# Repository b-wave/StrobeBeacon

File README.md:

# LED Strobe / Beacon
Strobe and beacon lights for models using PIC12F1822

This project describes a _realistic-looking_ set of lights for model aircraft. The strobe is typically a white light located at the aft end of the aircraft.  The strobe consists of several quick flashes, repeating after a dark pause. The beacon is a light that flashes once, typically as a red beacon at the top of the airplane's rudder, with a longer on-time duration You can also set up two alternating strobes, such a police or emergency vehicle, where the lights alternate between red and white or red and blue.

## Firmware
The firmware is included in the folder. It is a C source file that was compiled with the  _MPLAB IDE_ V6.00. The .HEX file can be directly programmed, either on the chip itself or using the provided in-circuit programming pins (ICP) on the. If you do not want to compile, you can directly use the provided .HEX file. We used a _TL866 II Plus_ for both. You can use the uploaded StrobeBeacon.X.production.HEX file.

## Hardware

The hardware was developed using KiCAD version 8.0.  

This is a simple circuit board. All the Gerber files are included, but you can order directly from this project file on OSH Park.com: 

https://oshpark.com/shared_projects/jd6ww6b6

## Enhancements
Several features can be added to this.  I will either expand here or make a new repo. 

First to make it useful in an R/C model, the ability to read an R/C receiver's PWM channel can be used switch the strobes on or off. Adding a standard 3-pin 0.1 inch connector allows for direct to an R/C receiver's channel connector. For an Arduino, it is relatively simple to use the pulseIn() from the standard libraries.
```C
byte GetPWM(byte pin)
{
  unsigned long highTime = pulseIn(pin, HIGH, 50000UL);  // 50 millisecond timeout
  unsigned long lowTime = pulseIn(pin, LOW, 50000UL);  // 50 millisecond timeout

  // pulseIn() returns zero on timeout
  if (highTime == 0 || lowTime == 0)
    return digitalRead(pin) ? 100 : 0;  // HIGH == 100%,  LOW = 0%

  return (100 * highTime) / (highTime + lowTime);  // highTime as percentage of total cycle time
}
```

But for a PIC microcontroller it is a little more involved.  We have to use timers and interrrupts.  The CCP1 interrupt can be used to detect the edge. Then the width is timed. 

*Copilot PROMPT: Give an example of pic12f1822 to measure a PWM input*

To measure a PWM input using the PIC12F1822 microcontroller, you can use the Capture/Compare/PWM (CCP) module. Here's a basic example of how you can set it up:

1. Configure the CCP module: Set the CCP module to capture mode to measure the PWM input signal.
2. Configure the Timer: Use Timer1 to capture the PWM signal's period and duty cycle.
3. Capture the PWM signal: Use the CCP module to capture the rising and falling edges of the PWM signal.

Here's a simple code example using MPLAB X IDE and XC8 compiler:
```C
#include <xc.h>

// Configuration bits
#pragma config FOSC = INTOSC    // Oscillator Selection
#pragma config WDTE = OFF       // Watchdog Timer Enable
#pragma config PWRTE = OFF      // Power-up Timer Enable
#pragma config MCLRE = ON       // MCLR Pin Function Select
#pragma config CP = OFF         // Flash Program Memory Code Protection
#pragma config BOREN = ON       // Brown-out Reset Enable
#pragma config CLKOUTEN = OFF   // Clock Out Enable
#pragma config IESO = ON        // Internal/External Switchover Mode
#pragma config FCMEN = ON       // Fail-Safe Clock Monitor Enable

void main(void) {
    // Initialize the oscillator
    OSCCON = 0x70; // Set internal oscillator to 8MHz

    // Configure CCP1 module for capture mode
    CCP1CON = 0x05; // Capture mode, every rising edge

    // Configure Timer1
    T1CON = 0x31; // Timer1 on, prescaler 1:8

    // Enable CCP1 interrupt
    PIE1bits.CCP1IE = 1;
    INTCONbits.PEIE = 1;
    INTCONbits.GIE = 1;
/*
Example of a channel used to control the Strobes 
Strobe AUX (CH8):
            Low     High      PWM%
power on    0       0         0%
switch off  995uS   18882uS   5%
switch on   1988uS  17888uS   10%
*/
    while (1) {
        // Main loop

    }
}

// CCP1 interrupt service routine
void __interrupt() CCP1_ISR(void) {
    if (PIR1bits.CCP1IF) {
        // Capture the PWM signal period and duty cycle
        unsigned int captureValue = CCPR1;
        PIR1bits.CCP1IF = 0; // Clear the interrupt flag
    }
}

```
This code sets up the PIC12F1822 to capture the rising edges of a PWM signal using the CCP1 module and Timer1. You can modify the code to capture both rising and falling edges to measure the duty cycle accurately.

For more details, you can refer to the PIC12F1822 datasheet.
We could also use ranges of PWM to select different modes. 

```C
While (1) {
//main loop
//Note: this assumes the pulse width numbers are predefined

byte mode
	{
 	 byte PWM = GetPWM(PWMPin);
   		 if (PWM < LOWPULSE_WIDTH) mode = 0;  //OFF
     			else if (PWM >=  LOWPULSE_WIDTH && PWM <=  LONGPULSE_WIDTH) mode = 1; //  Beacon/Strobe
     			  else if (PWM > LONGPULSE_WIDTTH) mode = 2; //Strobe/strobe
//... then use the mode byte to control the strobes  the get PWM probabily should be done in the long ( off)  time outs.
	}
}

```

Second, to make a proper navigation lights for a UAV the LEDs must be brighter.  Transistors can be added to the circuit to allow higher voltages for more powerfull the LEDs since navigation beacons should be seen for some distance.

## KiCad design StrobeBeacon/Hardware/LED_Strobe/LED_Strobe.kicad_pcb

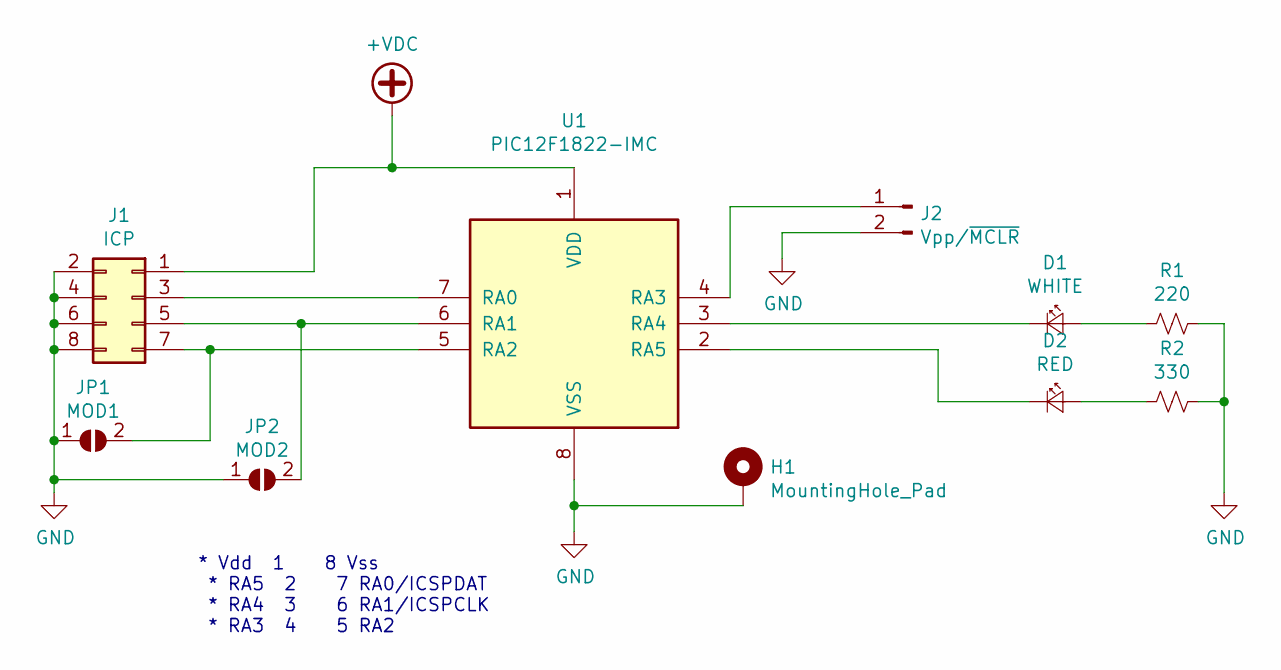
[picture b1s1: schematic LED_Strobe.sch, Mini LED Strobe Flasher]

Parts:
D1: WHITE; LED_D3.0mm_Clear
D2: RED; LED_D3.0mm
H1: MountingHole_Pad; MountingHole_3.2mm_M3_Pad_Via
J1: ICP; PinHeader_2x04_P2.54mm_Vertical
J2: Vpp/~MCLR; PinHeader_1x02_P2.54mm_Vertical
JP1: MOD1; SolderJumper-2_P1.3mm_Open_RoundedPad1.0x1.5mm
JP2: MOD2; SolderJumper-2_P1.3mm_Open_RoundedPad1.0x1.5mm
R1: 220; R_Axial_DIN0204_L3.6mm_D1.6mm_P2.54mm_Vertical
R2: 330; R_Axial_DIN0204_L3.6mm_D1.6mm_P2.54mm_Vertical
U1: PIC12F1822-IMC; DIP-8_W7.62mm

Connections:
+VDC: J1.1, U1.1 (VDD)
GND: H1.1, J1.2, J1.4, J1.6, J1.8, J2.2, JP1.1 (A), JP2.1 (A), R1.2, R2.2, U1.8 (VSS)
unnamed: D1.1 (K), U1.3 (RA4)
unnamed: D1.2 (A), R1.1
unnamed: D2.1 (K), U1.2 (RA5)
unnamed: D2.2 (A), R2.1
unnamed: J1.3, U1.7 (RA0)
unnamed: J1.5, JP2.2 (B), U1.6 (RA1)
unnamed: J1.7, JP1.2 (B), U1.5 (RA2)
unnamed: J2.1, U1.4 (RA3)

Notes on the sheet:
* Vdd 1 8 Vss * RA5 2 7 RA0/ICSPDAT * RA4 3 6 RA1/ICSPCLK * RA3 4 5 RA2

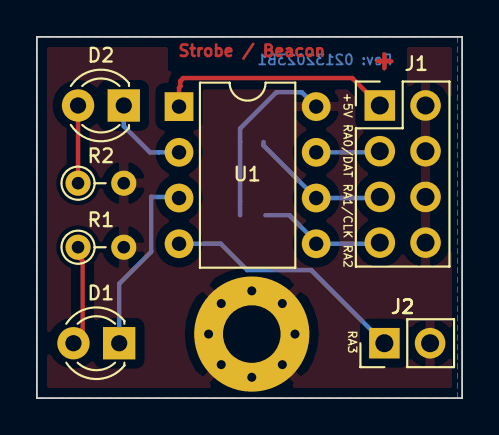
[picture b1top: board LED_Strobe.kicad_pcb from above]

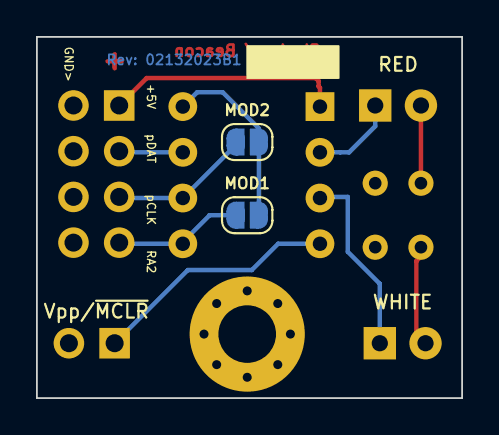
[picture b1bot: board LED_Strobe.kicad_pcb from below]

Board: 2 copper layers, 23.6 x 20.1 mm, 10 parts (2 on the bottom side), 10 nets.

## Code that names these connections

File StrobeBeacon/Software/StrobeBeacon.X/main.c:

/*
 * File:   main.c
 * Author: steve
 *
 * Created on January 18, 2023, 11:21 AM
 * 
 * Simulates Aircraft Strobe/Beacons
 * 
 * 
 * PIC12F1822 PINS:
 * Vdd  1    8 Vss
 * RA5  2    7 RA0/ICSPDAT
 * RA4  3    6 RA1/ICSPCLK
 * RA3  4    5 RA2  
 */


#include <xc.h>
#pragma config FOSC = INTOSC
#pragma config WDTE = OFF
#pragma config MCLRE = ON
#pragma config CLKOUTEN = OFF
#pragma config PLLEN = ON
#define _XTAL_FREQ 32000000

void main(void) { 
      TRISA2 = 1; //RA2 as Input PIN    
      TRISA3 = 1; //RA3 as Input PIN  
      TRISA4 = 0; //RA4 as Output PIN
      TRISA5 = 0; //RA5 as Output PIN
      
      OSCCON = 0b01110000; //32MHz
      ANSELA = 0;
      nWPUEN = 0;
      uint8_t i;
  while(RA3)
  {
  for( i=0; i<4; i++) {    
    RA5 = 1;  // White Strobe LED ON 
    __delay_ms(10); // 10 millisecond Delay
    RA5 = 0;  // LED OFF
    __delay_ms(100); // 10 millisecond Delay  
 }  
//LED 2 Beacon Mode
 if (RA2==1) {
    __delay_ms(200); // 500 millisecond Delay
     RA4 = 1;   //Red Beacon LED on
    __delay_ms(100); // 500 millisecond Delay
     RA4 = 0;  //LED off
    __delay_ms(200); // 00 millisecond Delay
    }
 //LED 2 Beacon Mode
 if (RA2==0) {
  for( i=0; i<4; i++) {    
    RA4 = 1;  // White Strobe LED ON 
    __delay_ms(10); // 10 millisecond Delay
    RA4 = 0;  // LED OFF
    __delay_ms(100); // 10 millisecond Delay  
        }  
      }
   
  }
    return;
}

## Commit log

2025-01-12 Add files via upload
    Hardware in KiCad 8.0 Firmware MPLAB X IDE V6.00
2025-01-13 Update README.md
    Updated and added schematic
2025-01-13 Update README.md
    Added OSH Park project link
2025-01-13 Update README.md
    Put in C example of possible PWM control (from a Prompt to Copilot)
2025-01-13 Update README.md
    edit list
